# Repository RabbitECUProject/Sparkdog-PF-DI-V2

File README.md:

# Sparkdog-PF-DI-V2
KiCad project for hardware development of Sparkdog PF-DI PCB. The Sparkdog PF-DI PCB can be used as a plug in PCB for the Rabbit ECU, extending the functionality to include:

1. Either Teensy 3.5 MK64 or MK10 processor, or both
2. 4 x Direct injection driver circuit
3. 2 x knock input circuit
4. 1 x 4-channel H-Bridge driver
5. 4 VVT input channels in addition to the Rabbit ECU Crank/Cam inputs
6. PIC18F26 stay-alive processor for can wake-up function

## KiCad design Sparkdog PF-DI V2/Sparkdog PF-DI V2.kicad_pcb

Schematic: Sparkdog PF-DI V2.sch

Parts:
C100: 0603 100nF; RESC1608X55N
J1, J3, J5: Conn_01x06_Female; SIP-6
J2, J4: Conn_01x08_Female; SIP-8
R100, R101: 0603 1k; RESC1608X55N
RN100, RN104, RN106: 1206 10k; 742C083103JP
RN101, RN102, RN103, RN105: 1206 1k; 742C083103JP
U2: Arduino_Footprint; ARDUINO_DUE

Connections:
/3 TEENSY/GDI1_SIG: RN100.3 (R3.1); also elsewhere on the board
/3 TEENSY/GDI2_SIG: RN100.4 (R4.1); also elsewhere on the board
/3 TEENSY/UART_RX_SIG: RN100.2 (R2.1); also elsewhere on the board
/3 TEENSY/UART_TX_SIG: RN100.1 (R1.1); also elsewhere on the board
/6 ETC PROCESSOR/A12: RN105.1 (R1.1), RN105.2 (R2.1); also elsewhere on the board
/7 POWER/SIG_CANH: J4.8; also elsewhere on the board
/7 POWER/SIG_CANL: J4.7; also elsewhere on the board
/7 POWER/SIG_KAL: J4.6; also elsewhere on the board
/ACH: U2.11; also elsewhere on the board
/ACL: U2.12; also elsewhere on the board
/ATS: U2.14; also elsewhere on the board
/BATT: U2.19; also elsewhere on the board
/CAN_RX: U2.23; also elsewhere on the board
/CAN_TX: U2.24; also elsewhere on the board
/CKPS_SIG: RN103.7 (R2.2), U2.71; also elsewhere on the board
/CMPS_SIG: RN103.8 (R1.2), U2.72; also elsewhere on the board
/CTS: U2.13; also elsewhere on the board
/DAC_UEGO: RN106.8 (R1.2), U2.22; also elsewhere on the board
/DCH: U2.9; also elsewhere on the board
/DCL: U2.10; also elsewhere on the board
/ETC_1A: R101.2, RN101.8 (R1.2); also elsewhere on the board
/ETC_1B: RN101.7 (R2.2); also elsewhere on the board
/ETC_2A: RN101.6 (R3.2); also elsewhere on the board
/ETC_2B: RN101.5 (R4.2); also elsewhere on the board
/ETC_O1A: J2.5; also elsewhere on the board
/ETC_O1B: J2.6; also elsewhere on the board
/ETC_O2A: J2.7; also elsewhere on the board
/ETC_O2B: J2.8; also elsewhere on the board
/GDI1_SIG_s: RN100.6 (R3.2), RN103.1 (R1.1); also elsewhere on the board
/GDI2_SIG_s: RN100.5 (R4.2), RN103.2 (R2.1); also elsewhere on the board
/HMEN: R101.1, U2.53; also elsewhere on the board
/HMF: U2.61
/HS1EN: U2.40; also elsewhere on the board
/HS2EN: U2.37; also elsewhere on the board
/HYSTHAB: U2.45; also elsewhere on the board
/HYSTLAB: U2.46; also elsewhere on the board
/IEN: U2.42; also elsewhere on the board
/IGT1_SIG: RN101.1 (R1.1), U2.76; also elsewhere on the board
/IGT2_SIG: RN101.2 (R2.1), U2.75; also elsewhere on the board
/IGT3_SIG: RN101.3 (R3.1), U2.74; also elsewhere on the board
/IGT4_SIG: RN101.4 (R4.1), U2.73; also elsewhere on the board
/INJ1_SIG: RN102.1 (R1.1), U2.82; also elsewhere on the board
/INJ2_SIG: RN102.2 (R2.1), U2.81; also elsewhere on the board
/INJ3_SIG: RN102.3 (R3.1), U2.80; also elsewhere on the board
/INJ4_SIG: RN102.4 (R4.1), U2.79; also elsewhere on the board
/M1EN: U2.58; also elsewhere on the board
/M2EN: U2.56; also elsewhere on the board
/MISO: U2.87; also elsewhere on the board
/MOSI: U2.91; also elsewhere on the board
/PPSM: U2.20; also elsewhere on the board
/PPSS: U2.16; also elsewhere on the board
/PUAEN: U2.51; also elsewhere on the board
/PUBEN: U2.36; also elsewhere on the board
/PUMP_PWM: J1.6; also elsewhere on the board
/PWIOA+: J1.5; also elsewhere on the board
/PWIOAB-: J1.3; also elsewhere on the board
/PWIOB+: J3.6; also elsewhere on the board
/PWIOC+: J5.5; also elsewhere on the board
/PWIOCD-: J1.4; also elsewhere on the board
/PWIOD+: J5.6; also elsewhere on the board
/REL_CS: U2.57; also elsewhere on the board
/REL_RST: R100.1, U2.55
/RPS: U2.18; also elsewhere on the board
/SCLK: U2.88; also elsewhere on the board
/SIGAB_HVEN: RN104.8 (R1.2); also elsewhere on the board
/SIGAB_PEAK: RN102.8 (R1.2); also elsewhere on the board
/SIGAB_PWM: RN102.7 (R2.2); also elsewhere on the board
/SIGCD_HVEN: RN104.7 (R2.2); also elsewhere on the board
/SIGCD_PEAK: RN102.6 (R3.2); also elsewhere on the board
/SIGCD_PWM: RN102.5 (R4.2); also elsewhere on the board
/SIG_K1IN: J2.3; also elsewhere on the board
/SIG_K2IN: J2.4; also elsewhere on the board
/SIG_VVTB_OUT: RN106.5 (R4.2); also elsewhere on the board
/SWH: RN104.1 (R1.1), U2.44; also elsewhere on the board
/SWL: RN104.2 (R2.1), U2.43; also elsewhere on the board
/TPSM: U2.17; also elsewhere on the board
/TPSS: U2.15; also elsewhere on the board
/UART_RX: RN100.7 (R2.2); also elsewhere on the board
/UART_TX: RN100.8 (R1.2); also elsewhere on the board
/VRAEN: U2.34; also elsewhere on the board
/VRBEN: U2.33; also elsewhere on the board
/VSDC: U2.27; also elsewhere on the board
/VVT_INP1: J3.3; also elsewhere on the board
/VVT_INP2: J3.4; also elsewhere on the board
/VVT_INP3: J5.3; also elsewhere on the board
/VVT_INP4: J5.4; also elsewhere on the board
unnamed: C100.2, RN106.1 (R1.1), RN106.2 (R2.1)
unnamed: RN106.3 (R3.1), RN106.4 (R4.1)
unnamed: RN106.6 (R3.2), RN106.7 (R2.2)
VBATT: J2.1; also elsewhere on the board
VCC3V3: R100.2, U2.4; also elsewhere on the board
VCC5V: RN105.8 (R1.2), U2.5, U2.59, U2.60, U2.92; also elsewhere on the board
VCC12VP: U2.8; also elsewhere on the board
VCC12VPP: J1.2; also elsewhere on the board
VSS: C100.1, J1.1, J2.2, RN105.7 (R2.2), U2.6, U2.7, U2.25, U2.26, U2.90; also elsewhere on the board

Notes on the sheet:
ALTERNATE SIGNAL BUS WHEN TEENSY NOT USED
OVERRIDE NO T3.5
ARDUINO FOOTPRINT ON RABBIT ECU PCB - USED AS GENERIC PLUG IN INTERFACE
3.3v RAIL OUTPUT TO RABBIT ECU
5.0V RAIL INPUT FROM RABBIT ECU
SHEET 1 MASTER SHEET 2 VVT SHEET 3 TEENSY SHEET 4 KNOCK SHEET 5 ETC SHEET 6 ETC PROCESSOR SHEET 7 POWER SHEET 8 GDI SHEET 9 GDI CONTROL
RC PWM to VOLT converter when T3.5 not used

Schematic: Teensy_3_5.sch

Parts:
D300, D301: 0805 LED; RESC2012X60N
RN300: 1206 1k; 742C083103JP
U300: Teensy_3_5; TEENSY_3_5

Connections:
/2 VVT/PULLEN_AB: U300.26; also elsewhere on the board
/3 TEENSY/GDI1_SIG: U300.30; also elsewhere on the board
/3 TEENSY/GDI2_SIG: U300.29; also elsewhere on the board
/3 TEENSY/REL_RST: U300.62
/3 TEENSY/UART_RX_SIG: U300.3; also elsewhere on the board
/3 TEENSY/UART_TX_SIG: U300.2; also elsewhere on the board
/ACH: U300.67; also elsewhere on the board
/ACL: U300.68; also elsewhere on the board
/BATT: U300.41; also elsewhere on the board
/CAN_RX: U300.6; also elsewhere on the board
/CAN_TX: U300.5; also elsewhere on the board
/CKPS_SIG: U300.28; also elsewhere on the board
/CMPS_SIG: U300.27; also elsewhere on the board
/CTS: U300.37; also elsewhere on the board
/DAC_UEGO: U300.32; also elsewhere on the board
/GDI_SEL: U300.20; also elsewhere on the board
/HMEN: U300.63; also elsewhere on the board
/HS1EN: U300.24; also elsewhere on the board
/HS2EN: U300.23; also elsewhere on the board
/HYSTHAB: U300.66; also elsewhere on the board
/HYSTLAB: U300.65; also elsewhere on the board
/IEN: U300.51; also elsewhere on the board
/IGT1_SIG: U300.11; also elsewhere on the board
/IGT2_SIG: U300.12; also elsewhere on the board
/IGT3_SIG: U300.21; also elsewhere on the board
/IGT4_SIG: U300.22; also elsewhere on the board
/INJ1_SIG: U300.7; also elsewhere on the board
/INJ2_SIG: U300.8; also elsewhere on the board
/INJ3_SIG: U300.9; also elsewhere on the board
/INJ4_SIG: U300.10; also elsewhere on the board
/M1EN: U300.59; also elsewhere on the board
/M2EN: U300.61; also elsewhere on the board
/MISO: U300.54; also elsewhere on the board
/MOSI: U300.53; also elsewhere on the board
/PPSM: U300.31; also elsewhere on the board
/PPSS: U300.38; also elsewhere on the board
/PUAEN: U300.64; also elsewhere on the board
/PUBEN: U300.56; also elsewhere on the board
/REL_CS: U300.60; also elsewhere on the board
/RPS: U300.40; also elsewhere on the board
/SCLK: U300.55; also elsewhere on the board
/SIG_GDIP_EN: U300.4; also elsewhere on the board
/SIG_PUMP_EN: U300.35; also elsewhere on the board
/SIG_VVT1_IN: U300.45; also elsewhere on the board
/SIG_VVT2_IN: U300.44; also elsewhere on the board
/SIG_VVT3_IN: U300.43; also elsewhere on the board
/SIG_VVT4_IN: U300.42; also elsewhere on the board
/SIG_VVTA_OUT: U300.36; also elsewhere on the board
/SWH: RN300.8 (R1.2), U300.49; also elsewhere on the board
/SWL: RN300.7 (R2.2), U300.50; also elsewhere on the board
/TPSM: U300.39; also elsewhere on the board
/TPSS: U300.25; also elsewhere on the board
/VRAEN: U300.57; also elsewhere on the board
/VRBEN: U300.58; also elsewhere on the board
/VSDC: U300.33; also elsewhere on the board
unnamed: D300.2 (A), RN300.4 (R4.1)
unnamed: D301.2 (A), RN300.3 (R3.1)
unnamed: RN300.5 (R4.2), U300.19
unnamed: RN300.6 (R3.2), U300.18
VCC3V3: U300.15, U300.46; also elsewhere on the board
VCC5V: RN300.1 (R1.1), U300.48; also elsewhere on the board
VSS: D300.1 (K), D301.1 (K), RN300.2 (R2.1), U300.1, U300.34, U300.47; also elsewhere on the board

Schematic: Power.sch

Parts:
C700: 0603 100nF; RESC1608X55N
C701, C702: 0603 10pF; RESC1608X55N
CD700, CD701, CD703, CD705, CD706, CD708, CD710, CD712, CD713, CD714: 0603 100nF; RESC1608X55N
CD702, CD704, CD707, CD711: CAP4mm 4.7uF; CAPAE430X550N
CD709: CAP17mm; CAPAE1700X1700N
D700: BYG22B; DIOM5127X229N
J700: SSM-106-L-SV; SSM106LSV; Mouser Part Number 200-SSM106LSV
L700, L701: 0805 10nH; RESC2012X60N
L702: SRN8040-680; INDC8566X410N
R700, R701, R706: 0603 1k; RESC1608X55N
R702, R703: 0603 22k; RESC1608X55N
R704: 2512 1R; RESC6331X75N
R705: 0603 100k; RESC1608X55N
U700, U703: BD433M5FP-CE2; MDAC-TO-252-3; Mouser Part Number 755-BD433M5FP-CE2
U701: PIC18F26J50T-I_ML; PIC18F26; Mouser Part Number 579-PIC18F26J50T-IML
U702: TCAN334; SOIC127P600X175-8N
U704: LM2577SX-ADJ_NOPB; KTT0005B; Mouser Part Number 926-LM2577SXADJNOPB
X700: 4 MHz; ECS49205PXTR

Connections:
/7 POWER/SIG_CANH: U702.7 (CANH); also elsewhere on the board
/7 POWER/SIG_CANL: U702.6 (CANL); also elsewhere on the board
/7 POWER/SIG_KAL: U701.1; also elsewhere on the board
/GDI_SEL: R705.2; also elsewhere on the board
/SIG_K1O: U701.10; also elsewhere on the board
/SIG_K2O: U701.28; also elsewhere on the board
/SIG_KTX: U701.14; also elsewhere on the board
unnamed: C700.1, R700.2
unnamed: C701.1, U701.6, X700.1
unnamed: C702.1, U701.7, X700.2
unnamed: CD709.1, D700.1 (K), R703.1, R704.2
unnamed: CD714.1, U701.3
unnamed: D700.2 (A), L702.2, U704.4 (SWITCH)
unnamed: J700.1, R706.2, U701.26
unnamed: J700.4, U701.25
unnamed: J700.5, U701.24
unnamed: R700.1, U704.1 (COMP)
unnamed: R701.2, R702.2, U704.2 (FEEDBACK)
unnamed: R702.1, R703.2
unnamed: R705.1, U701.2
unnamed: U701.19, U702.8 (STB)
unnamed: U701.20, U702.5 (SHDN)
unnamed: U701.21, U702.4 (RXD)
unnamed: U701.23, U702.1 (TXD)
VBATT: CD712.2, U703.1 (VCC); also elsewhere on the board
VCC3V3: CD701.2, CD703.2, CD704.1, J700.2, L701.2, U700.3 (VOUT); also elsewhere on the board
VCC3V3K: CD706.1, CD707.1, CD708.1, CD713.2, U701.17, U702.3 (VCC), U703.3 (VOUT)
VCC12VP: CD700.1, CD702.1, U700.1 (VCC); also elsewhere on the board
VCC12VPP: CD710.1, CD711.1, L702.1, U704.5 (VIN); also elsewhere on the board
VCC50VPP: R704.1; also elsewhere on the board
VCCA3V3: CD705.2, L701.1; also elsewhere on the board
VSS: C700.2, C701.2, C702.2, CD700.2, CD701.1, CD702.2, CD703.1, CD704.2, CD706.2, CD707.2, CD708.2, CD709.2, CD710.2, CD711.2, CD712.1, CD713.1, CD714.2, J700.3, L700.2, R701.1, U700.2 (N.C.), U701.5, U701.16, U701.29, U702.2 (GND), U703.2 (N.C.), U704.3 (GND_1), U704.6 (GND_2); also elsewhere on the board
VSSA: CD705.1, L700.1; also elsewhere on the board
uC_RESET: R706.1; also elsewhere on the board

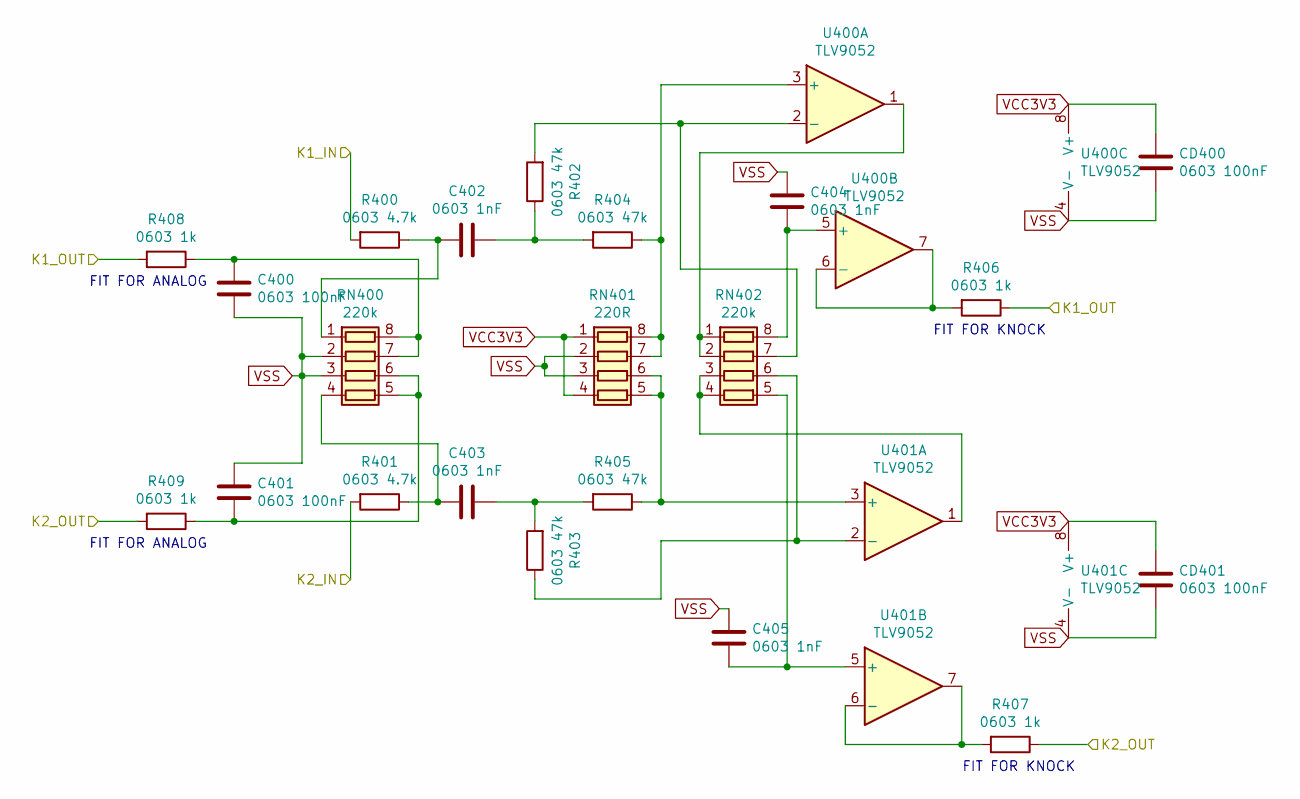
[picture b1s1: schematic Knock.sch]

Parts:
C400, C401: 0603 100nF; RESC1608X55N
C402, C403, C404, C405: 0603 1nF; RESC1608X55N
CD400, CD401: 0603 100nF; RESC1608X55N
R400, R401: 0603 4.7k; RESC1608X55N
R402, R403, R404, R405: 0603 47k; RESC1608X55N
R406, R407, R408, R409: 0603 1k; RESC1608X55N
RN400, RN402: 220k; 742C083103JP
RN401: 220R; 742C083103JP
U400, U401: TLV9052; SOT65P280X110-8N

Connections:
/SIG_K1IN: R400.2; also elsewhere on the board
/SIG_K1O: R406.1, R408.2; also elsewhere on the board
/SIG_K2IN: R401.2; also elsewhere on the board
/SIG_K2O: R407.1, R409.2; also elsewhere on the board
unnamed: C400.1, R408.1, RN400.7 (R2.2), RN400.8 (R1.2)
unnamed: C401.2, R409.1, RN400.5 (R4.2), RN400.6 (R3.2)
unnamed: C402.1, R402.1, R404.2
unnamed: C402.2, R400.1, RN400.1 (R1.1)
unnamed: C403.1, R403.2, R405.2
unnamed: C403.2, R401.1, RN400.4 (R4.1)
unnamed: C404.2, RN402.8 (R1.2), U400.5 (+)
unnamed: C405.2, RN402.5 (R4.2), U401.5 (+)
unnamed: R402.2, RN402.7 (R2.2), U400.2 (-)
unnamed: R403.1, RN402.6 (R3.2), U401.2 (-)
unnamed: R404.1, RN401.7 (R2.2), RN401.8 (R1.2), U400.3 (+)
unnamed: R405.1, RN401.5 (R4.2), RN401.6 (R3.2), U401.3 (+)
unnamed: R406.2, U400.6 (-), U400.7
unnamed: R407.2, U401.6 (-), U401.7
unnamed: RN402.1 (R1.1), RN402.2 (R2.1), U400.1
unnamed: RN402.3 (R3.1), RN402.4 (R4.1), U401.1
VCC3V3: CD400.1, CD401.1, RN401.1 (R1.1), RN401.4 (R4.1), U400.8 (V+), U401.8 (V+); also elsewhere on the board
VSS: C400.2, C401.1, C404.1, C405.1, CD400.2, CD401.2, RN400.2 (R2.1), RN400.3 (R3.1), RN401.2 (R2.1), RN401.3 (R3.1), U400.4 (V-), U401.4 (V-); also elsewhere on the board

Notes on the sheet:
FIT FOR KNOCK
FIT FOR ANALOG

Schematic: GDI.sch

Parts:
D800, D802, D803, D805, D850, D852, D853: DO-214AC SCHOTTKY; DIOM5127X229N
D801, D804, D851: DO-214AC 81V; DIOM5127X229N
R800, R850: 0603 470R; RESC1608X55N
R801, R851: 1206 4.7k; RESC3216X60N
R802, R852: 2512 0.05R; RESC6331X75N
R803, R805, R808, R809, R812, R853, R855, R858, R859: 0603 10k; RESC1608X55N
R804, R806, R854, R856: 0603 4.7k; RESC1608X55N
R807, R857: 0603 1k; RESC1608X55N
R810: 2512 0.2R; RESC6331X75N
R811: 0603 220R; RESC1608X55N
U800, U801, U802, U850, U851, U852: DDC113TU; SOT-363-6
U803, U804, U810, U811, U853, U854: STD7NK40Z; MDAC-TO-252-3
U805, U806, U807, U808, U855, U856, U857, U858: SUD19P06-60; MDAC-TO-252-3
U809: Dual_Trans_Array_NPN; SOT-363-6

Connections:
/8 GDI/SIG_12V_HSSA: R805.2, U800.6, U806.1 (G)
/8 GDI/SIG_12V_HSSB: R808.2, U800.3, U807.1 (G)
/8 GDI/SIG_12V_HSSC: R855.2, U850.6, U856.1 (G)
/8 GDI/SIG_12V_HSSD: R858.2, U850.3, U857.1 (G)
/8 GDI/SIG_HV_HSSA: R803.1, R804.2, U805.1 (G)
/8 GDI/SIG_HV_HSSB: R806.2, R809.1, U808.1 (G)
/8 GDI/SIG_HV_HSSC: R853.1, R854.2, U855.1 (G)
/8 GDI/SIG_HV_HSSD: R856.2, R859.1, U858.1 (G)
/8 GDI/SIG_PUMP_PWMS: R811.2; also elsewhere on the board
/8 GDI/SIG_PWM_LSAB_s: R800.1, U802.3, U803.1 (G)
/8 GDI/SIG_PWM_LSCD_s: R850.1, U852.3, U853.1 (G)
/9 GDI CONTROL/SIGAB_LS_EN: R800.2; also elsewhere on the board
/9 GDI CONTROL/SIGA_HV_EN: U801.2; also elsewhere on the board
/9 GDI CONTROL/SIGB_HV_EN: U801.5; also elsewhere on the board
/9 GDI CONTROL/SIGB_LV_EN: U800.5; also elsewhere on the board
/9 GDI CONTROL/SIGCD_LS_EN: R850.2; also elsewhere on the board
/9 GDI CONTROL/SIGC_HV_EN: U851.2; also elsewhere on the board
/9 GDI CONTROL/SIGD_HV_EN: U851.5; also elsewhere on the board
/9 GDI CONTROL/SIGD_LV_EN: U850.5; also elsewhere on the board
/GDI1_SIG_s: U802.2; also elsewhere on the board
/GDI2_SIG_s: U852.2; also elsewhere on the board
/PUMP_PWM: D804.1 (K), D805.2 (A), R812.2, U810.2 (D); also elsewhere on the board
/PWIOA+: D802.1 (K), U805.2 (D); also elsewhere on the board
/PWIOAB-: D800.2 (A), D801.1 (K), R801.1, U803.2 (D); also elsewhere on the board
/PWIOB+: D803.1 (K), U808.2 (D); also elsewhere on the board
/PWIOC+: D852.1 (K), U855.2 (D); also elsewhere on the board
/PWIOCD-: D850.2 (A), D851.1 (K), R851.1, U853.2 (D); also elsewhere on the board
/PWIOD+: D853.1 (K), U858.2 (D); also elsewhere on the board
/SIGAB_IF: R807.2; also elsewhere on the board
/SIGAB_LVEN: U800.2; also elsewhere on the board
/SIGCD_IF: R857.2; also elsewhere on the board
/SIGCD_LVEN: U850.2; also elsewhere on the board
/SIG_PUMP_EN: U809.2; also elsewhere on the board
/SIG_PUMP_IF: R810.2, U809.5, U810.3 (S); also elsewhere on the board
unnamed: D800.1 (K), U804.2 (D)
unnamed: D802.2 (A), U806.2 (D)
unnamed: D803.2 (A), U807.2 (D)
unnamed: D805.1 (K), U811.2 (D)
unnamed: D850.1 (K), U854.2 (D)
unnamed: D852.2 (A), U856.2 (D)
unnamed: D853.2 (A), U857.2 (D)
unnamed: R801.2, U802.6, U804.1 (G)
unnamed: R802.2, R807.1, U802.5, U803.3 (S)
unnamed: R803.2, U801.6
unnamed: R809.2, U801.3
unnamed: R811.1, U809.3, U810.1 (G)
unnamed: R812.1, U809.6, U811.1 (G)
unnamed: R851.2, U852.6, U854.1 (G)
unnamed: R852.2, R857.1, U852.5, U853.3 (S)
unnamed: R853.2, U851.6
unnamed: R859.2, U851.3
VCC12VPP: R805.1, R808.1, R855.1, R858.1, U804.3 (S), U806.3 (S), U807.3 (S), U811.3 (S), U854.3 (S), U856.3 (S), U857.3 (S); also elsewhere on the board
VCC50VPP: R804.1, R806.1, R854.1, R856.1, U805.3 (S), U808.3 (S), U855.3 (S), U858.3 (S); also elsewhere on the board
VSS: D801.2 (A), D804.2 (A), D851.2 (A), R802.1, R810.1, R852.1, U800.1, U800.4, U801.1, U801.4, U802.1, U802.4, U809.1, U809.4, U850.1, U850.4, U851.1, U851.4, U852.1, U852.4; also elsewhere on the board

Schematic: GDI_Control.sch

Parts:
CD900, CD901, CD902, CD903: 0603 100nF; RESC1608X55N
U900, U901: SN74AHCT02; SOP65P640X110-14N
U902, U903: SN74AHCT08; SOP65P640X110-14N

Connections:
/8 GDI/SIG_PUMP_PWMS: U902.8; also elsewhere on the board
/9 GDI CONTROL/SIGAB_LS_EN: U900.13; also elsewhere on the board
/9 GDI CONTROL/SIGA_HV_EN: U902.6; also elsewhere on the board
/9 GDI CONTROL/SIGB_HV_EN: U902.3; also elsewhere on the board
/9 GDI CONTROL/SIGB_LV_EN: U900.4; also elsewhere on the board
/9 GDI CONTROL/SIGCD_LS_EN: U901.13; also elsewhere on the board
/9 GDI CONTROL/SIGC_HV_EN: U903.6; also elsewhere on the board
/9 GDI CONTROL/SIGD_HV_EN: U903.3; also elsewhere on the board
/9 GDI CONTROL/SIGD_LV_EN: U901.4; also elsewhere on the board
/SIGAB_HVEN: U900.2, U900.3, U902.4; also elsewhere on the board
/SIGAB_LVEN: U900.5, U900.6; also elsewhere on the board
/SIGAB_PEAK: U900.8, U902.2, U902.5; also elsewhere on the board
/SIGAB_PWM: U900.9; also elsewhere on the board
/SIGCD_HVEN: U901.2, U901.3, U903.4; also elsewhere on the board
/SIGCD_LVEN: U901.5, U901.6; also elsewhere on the board
/SIGCD_PEAK: U901.8, U903.2, U903.5; also elsewhere on the board
/SIGCD_PWM: U901.9; also elsewhere on the board
/SIG_GDIP_EN: U902.9, U902.10; also elsewhere on the board
unnamed: U900.1, U902.1
unnamed: U900.10, U900.11, U900.12
unnamed: U901.1, U903.1
unnamed: U901.10, U901.11, U901.12
VCC5V: CD900.1, CD901.1, CD902.1, CD903.1, U900.14, U901.14, U902.12, U902.13, U902.14, U903.9, U903.10, U903.12, U903.13, U903.14; also elsewhere on the board
VSS: CD900.2, CD901.2, CD902.2, CD903.2; also elsewhere on the board

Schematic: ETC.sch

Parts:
C500, C501, C502: 0603 10nF; RESC1608X55N
C503, C504: 0603 100nF; RESC1608X55N
C505, C506: 0805 10uF; RESC2012X60N
CD500: CAP4mm 4.7uF; CAPAE1700X1700N
CD501, CD502: 0603 100nF; RESC1608X55N
D500, D501, D502, D503, D504: 0805 1N4148; RESC2012X60N
R500, R501: 0603 100k; RESC1608X55N
R502, R503: 0603 1k; RESC1608X55N
R504, R505: 2512 0.1R; RESC6331X75N
R506: 0603 100R; RESC1608X55N
R507, R508, R509, R510: 0805 0R; RESC2012X60N
R511: 0603 10k; RESC1608X55N
R512: 0603 47k; RESC1608X55N
R513: 0603 820k; RESC1608X55N
R514: 0603 5M; RESC1608X55N
R515: 0603 470k; RESC1608X55N
RN500: 1206 180k; 742C083103JP
RN501: 1206 10k; 742C083103JP
U500: L6206PD013TR; SOP65P1420X360-37N; Mouser Part Number 511-L6206PD013TR
U501: SUD19P06-60; MDAC-TO-252-3
U502: TL331SN4T3G; SOT95P275X110-5N; Mouser Part Number 863-TL331SN4T3G
U503: Dual_Trans_Array_NPN; SOT-363-6

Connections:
/5 ETC/ETC_ENA: D502.2 (A), R500.2; also elsewhere on the board
/5 ETC/ETC_ENB: D503.2 (A), R501.2; also elsewhere on the board
/5 ETC/ETC_PEN: R511.2, U501.1 (G), U503.6
/5 ETC/VBOOT: C503.2, C504.2, D501.1 (K), U500.30 (VBOOT)
/5 ETC/VCC_ETC: C503.1, C504.1, CD500.1, CD501.2, D500.2 (A), U500.4 (VSA), U500.33 (VSB), U501.2 (D)
/5 ETC/VCP: C502.2, U500.7 (VCP)
/ETC_1A: R509.1, U500.10 (IN1A); also elsewhere on the board
/ETC_1B: R510.1, U500.26 (IN1B); also elsewhere on the board
/ETC_2A: R509.2, U500.11 (IN2A); also elsewhere on the board
/ETC_2B: R510.2, U500.27 (IN2B); also elsewhere on the board
/ETC_IFA: R504.1, U500.12 (SENSEA); also elsewhere on the board
/ETC_IFB: R505.1, U500.25 (SENSEB); also elsewhere on the board
/ETC_O1A: R507.1, U500.15 (OUT1A); also elsewhere on the board
/ETC_O1B: R508.1, U500.22 (OUT1B); also elsewhere on the board
/ETC_O2A: R507.2, U500.5 (OUT2A); also elsewhere on the board
/ETC_O2B: R508.2, U500.32 (OUT2B); also elsewhere on the board
/PPSM: RN500.1 (R1.1); also elsewhere on the board
/TPSM: R512.1, RN500.4 (R4.1); also elsewhere on the board
unnamed: C500.1, R500.1, U500.8 (ENA), U500.13 (OCDA)
unnamed: C501.1, R501.1, U500.24 (OCDB), U500.29 (ENB)
unnamed: C502.1, R506.2
unnamed: C505.2, RN500.7 (R2.2), RN500.8 (R1.2), U502.1 (IN-)
unnamed: C506.1, D504.2 (A), R513.1, R514.2, RN500.5 (R4.2), RN500.6 (R3.2), U502.3 (IN+)
unnamed: D500.1 (K), D501.2 (A), R506.1
unnamed: D502.1 (K), RN501.1 (R1.1)
unnamed: D503.1 (K), RN501.2 (R2.1)
unnamed: D504.1 (K), R512.2
unnamed: R502.1, U500.9 (PROGCLA)
unnamed: R503.2, U500.28 (PROGCLB)
unnamed: R514.1, R515.2, U502.4 (OUT), U503.5
unnamed: RN501.3 (R3.1), RN501.4 (R4.1)
unnamed: RN501.6 (R3.2), RN501.7 (R2.2), RN501.8 (R1.2), U503.2, U503.3
VCC5V: CD502.1, R515.1, U502.5 (VCC); also elsewhere on the board
VCC12VPP: R511.1, U501.3 (S); also elsewhere on the board
VSS: C500.2, C501.2, C505.1, C506.2, CD500.2, CD501.1, CD502.2, R502.2, R503.1, R504.2, R505.2, R513.2, RN500.2 (R2.1), RN500.3 (R3.1), RN501.5 (R4.2), U500.1 (GND_1), U500.18 (GND_2), U500.19 (GND_3), U500.36 (GND_4), U500.37 (EP), U502.2 (VEE), U503.1, U503.4; also elsewhere on the board

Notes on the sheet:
TODO CHANGE TO FET

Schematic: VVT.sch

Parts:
C200, C201, C202, C203: 0603 1nF; RESC1608X55N
CD200: 0603 100nF; RESC1608X55N
D200, D201, D202, D203: BZX84C5V1LT1G; SOT96P237X111-3N; Mouser Part Number 863-BZX84C5V1LT1G
R200, R201: 1206 0.1R; RESC3216X60N
RN200, RN201, RN202, RN204, RN205: 1206 10k; 742C083103JP
RN203: 1206 470R; 742C083103JP
U200: IRF7907TRPBF; SOIC127P600X175-8N; Mouser Part Number 942-IRF7907TRPBF
U201, U202: Dual_Trans_Array_NPN; SOT-363-6
U203, U204: Dual_Trans_Array_PNP; SOT-363-6
U205: 74AHC14PW,118; SOP65P640X110-14N; Mouser Part Number 771-74AHC14PW-T

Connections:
/2 VVT/OUT_VVTA: U200.7 (D2_1), U200.8 (D2_2)
/2 VVT/OUT_VVTB: U200.5 (D1_1), U200.6 (D1_2)
/2 VVT/PULLEN_AB: U201.2, U201.5, U202.2, U202.5; also elsewhere on the board
/2 VVT/VVTA_FB: RN200.1 (R1.1)
/2 VVT/VVTB_FB: RN200.3 (R3.1)
/SIG_VVT1_IN: RN201.2 (R2.1), RN201.3 (R3.1); also elsewhere on the board
/SIG_VVT2_IN: RN202.2 (R2.1), RN202.3 (R3.1); also elsewhere on the board
/SIG_VVT3_IN: RN204.6 (R3.2), RN204.7 (R2.2); also elsewhere on the board
/SIG_VVT4_IN: RN205.6 (R3.2), RN205.7 (R2.2); also elsewhere on the board
/SIG_VVTA_OUT: RN200.2 (R2.1); also elsewhere on the board
/SIG_VVTB_OUT: RN200.4 (R4.1); also elsewhere on the board
/VVT_INP1: RN201.1 (R1.1), RN203.2 (R2.1); also elsewhere on the board
/VVT_INP2: RN202.1 (R1.1), RN203.1 (R1.1); also elsewhere on the board
/VVT_INP3: RN203.4 (R4.1), RN204.8 (R1.2); also elsewhere on the board
/VVT_INP4: RN203.3 (R3.1), RN205.8 (R1.2); also elsewhere on the board
unnamed: C200.2, D200.3 (K), RN201.8 (R1.2), U205.1 (1A)
unnamed: C201.1, D201.3 (K), RN202.8 (R1.2), U205.5 (3A)
unnamed: C202.2, D202.3 (K), RN204.1 (R1.1), U205.13 (6A)
unnamed: C203.1, D203.3 (K), RN205.1 (R1.1), U205.9 (4A)
unnamed: R200.2, RN200.8 (R1.2), U200.1 (S2)
unnamed: R201.1, RN200.6 (R3.2), U200.3 (S1)
unnamed: RN200.5 (R4.2), U200.4 (G1)
unnamed: RN200.7 (R2.2), U200.2 (G2)
unnamed: RN201.5 (R4.2), RN201.6 (R3.2)
unnamed: RN201.7 (R2.2), U205.2 (1Y), U205.3 (2A)
unnamed: RN202.5 (R4.2), RN202.6 (R3.2)
unnamed: RN202.7 (R2.2), U205.6 (3Y)
unnamed: RN203.5 (R4.2), U204.6
unnamed: RN203.6 (R3.2), U204.3
unnamed: RN203.7 (R2.2), U203.6
unnamed: RN203.8 (R1.2), U203.3
unnamed: RN204.2 (R2.1), U205.12 (6Y)
unnamed: RN204.3 (R3.1), RN204.4 (R4.1)
unnamed: RN205.2 (R2.1), U205.8 (4Y)
unnamed: RN205.3 (R3.1), RN205.4 (R4.1)
unnamed: U201.3, U203.2
unnamed: U201.6, U203.5
unnamed: U202.3, U204.2
unnamed: U202.6, U204.5
VCC5V: CD200.1, U203.1, U203.4, U204.1, U204.4, U205.14 (VCC); also elsewhere on the board
VSS: C200.1, C201.2, C202.1, C203.2, CD200.2, D200.1 (A), D201.1 (A), D202.1 (A), D203.1 (A), R200.1, R201.2, RN201.4 (R4.1), RN202.4 (R4.1), RN204.5 (R4.2), RN205.5 (R4.2), U201.1, U201.4, U202.1, U202.4, U205.7 (GND); also elsewhere on the board

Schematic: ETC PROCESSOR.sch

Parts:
C600, C601: 0603 10pF; RESC1608X55N
CD600, CD601, CD602, CD603, CD604, CD605, CD606: 0603 100nF; RESC1608X55N
J600: M50-3610542R; M503610542; Mouser Part Number 855-M50-3610542R
R600, R601: 0603 1k; RESC1608X55N
RN600, RN602, RN603, RN605, RN606: 1206 10k; 742C083103JP
RN601: 1206 100k; 742C083103JP
RN604: 1206 1k; 742C083103JP
U600: MK10DX128VLK7
U601: TLV809EA29DCKR; SOT65P210X110-3N; Mouser Part Number 595-TLV809EA29DCKR
X600: Crystal; ECS49205PXTR

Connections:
/5 ETC/ETC_ENA: U600.52; also elsewhere on the board
/5 ETC/ETC_ENB: U600.71; also elsewhere on the board
/6 ETC PROCESSOR/A12: RN606.3 (R3.1); also elsewhere on the board
/6 ETC PROCESSOR/EZP_DI: J600.8, U600.27
/6 ETC PROCESSOR/GDI_LR: RN604.5 (R4.2), U600.72
/6 ETC PROCESSOR/RESET: J600.10, R600.2, U600.42
/6 ETC PROCESSOR/SWCLK: J600.4, U600.26
/6 ETC PROCESSOR/SWDIO: J600.2, U600.29
/6 ETC PROCESSOR/SWO: J600.6, U600.28
/ACH: RN601.1 (R1.1); also elsewhere on the board
/ACL: RN601.2 (R2.1); also elsewhere on the board
/ATS: RN605.6 (R3.2); also elsewhere on the board
/BATT: RN600.3 (R3.1); also elsewhere on the board
/CTS: RN605.5 (R4.2); also elsewhere on the board
/DCH: RN601.3 (R3.1); also elsewhere on the board
/DCL: RN601.4 (R4.1); also elsewhere on the board
/ETC_1A: U600.43; also elsewhere on the board
/ETC_1B: U600.44; also elsewhere on the board
/ETC_2A: U600.77; also elsewhere on the board
/ETC_2B: U600.78; also elsewhere on the board
/ETC_IFA: U600.45; also elsewhere on the board
/ETC_IFB: U600.46; also elsewhere on the board
/GDI1_SIG_s: U600.79; also elsewhere on the board
/GDI2_SIG_s: U600.80; also elsewhere on the board
/GDI_SEL: RN604.4 (R4.1); also elsewhere on the board
/IEN: RN603.6 (R3.2); also elsewhere on the board
/M1EN: RN603.7 (R2.2); also elsewhere on the board
/M2EN: RN603.8 (R1.2); also elsewhere on the board
/MISO: RN604.2 (R2.1); also elsewhere on the board
/MOSI: RN604.3 (R3.1); also elsewhere on the board
/PPSM: RN600.4 (R4.1); also elsewhere on the board
/PPSS: RN605.8 (R1.2); also elsewhere on the board
/PUAEN: RN602.5 (R4.2); also elsewhere on the board
/PUBEN: RN602.6 (R3.2); also elsewhere on the board
/REL_CS: RN603.5 (R4.2); also elsewhere on the board
/RPS: RN600.2 (R2.1); also elsewhere on the board
/SCLK: RN604.1 (R1.1); also elsewhere on the board
/SIGAB_HVEN: U600.30; also elsewhere on the board
/SIGAB_IF: U600.47; also elsewhere on the board
/SIGAB_LVEN: U600.33; also elsewhere on the board
/SIGAB_PEAK: U600.56; also elsewhere on the board
/SIGAB_PWM: U600.57; also elsewhere on the board
/SIGCD_HVEN: U600.32; also elsewhere on the board
/SIGCD_IF: U600.48; also elsewhere on the board
/SIGCD_LVEN: U600.34; also elsewhere on the board
/SIGCD_PEAK: U600.58; also elsewhere on the board
/SIGCD_PWM: U600.53; also elsewhere on the board
/SIG_K1O: RN606.1 (R1.1); also elsewhere on the board
/SIG_K2O: RN606.2 (R2.1); also elsewhere on the board
/SIG_KTX: R601.2; also elsewhere on the board
/SIG_PUMP_IF: U600.55; also elsewhere on the board
/SIG_VVTB_OUT: U600.54; also elsewhere on the board
/TPSM: RN600.1 (R1.1); also elsewhere on the board
/TPSS: RN605.7 (R2.2); also elsewhere on the board
/UART_RX: U600.5; also elsewhere on the board
/UART_TX: U600.6; also elsewhere on the board
/VRAEN: RN602.7 (R2.2); also elsewhere on the board
/VRBEN: RN602.8 (R1.2); also elsewhere on the board
/VSDC: RN606.4 (R4.1); also elsewhere on the board
unnamed: C600.2, U600.41, X600.1
unnamed: C601.2, U600.40, X600.2
unnamed: R601.1, U600.51
unnamed: RN600.5 (R4.2), U600.4
unnamed: RN600.6 (R3.2), U600.3
unnamed: RN600.7 (R2.2), U600.2
unnamed: RN600.8 (R1.2), U600.1
unnamed: RN601.5 (R4.2), U600.16
unnamed: RN601.6 (R3.2), U600.15
unnamed: RN601.7 (R2.2), U600.14
unnamed: RN601.8 (R1.2), U600.13
unnamed: RN602.1 (R1.1), U600.76
unnamed: RN602.2 (R2.1), U600.75
unnamed: RN602.3 (R3.1), U600.74
unnamed: RN602.4 (R4.1), U600.73
unnamed: RN603.1 (R1.1), U600.64
unnamed: RN603.2 (R2.1), U600.63
unnamed: RN603.3 (R3.1), U600.62
unnamed: RN603.4 (R4.1), U600.61
unnamed: RN604.6 (R3.2), U600.37
unnamed: RN604.7 (R2.2), U600.36
unnamed: RN604.8 (R1.2), U600.35
unnamed: RN605.1 (R1.1), U600.68
unnamed: RN605.2 (R2.1), U600.67
unnamed: RN605.3 (R3.1), U600.66
unnamed: RN605.4 (R4.1), U600.65
unnamed: RN606.5 (R4.2), U600.12
unnamed: RN606.6 (R3.2), U600.11
unnamed: RN606.7 (R2.2), U600.10
unnamed: RN606.8 (R1.2), U600.9
VCC3V3: CD600.1, CD601.2, CD602.1, CD604.1, CD605.2, CD606.1, J600.1, U600.7, U600.38, U600.50, U600.60, U600.70, U601.3 (VDD); also elsewhere on the board
VCCA3V3: CD603.2, U600.17, U600.18; also elsewhere on the board
VSS: C600.1, C601.1, CD600.2, CD601.1, CD602.2, CD604.2, CD605.1, CD606.2, J600.3, J600.5, J600.9, U600.8, U600.39, U600.49, U600.59, U600.69, U601.1 (GND); also elsewhere on the board
VSSA: CD603.1, U600.19, U600.20; also elsewhere on the board
uC_RESET: R600.1, U601.2 (~RESET); also elsewhere on the board

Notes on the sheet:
DEBUG SWD PORT

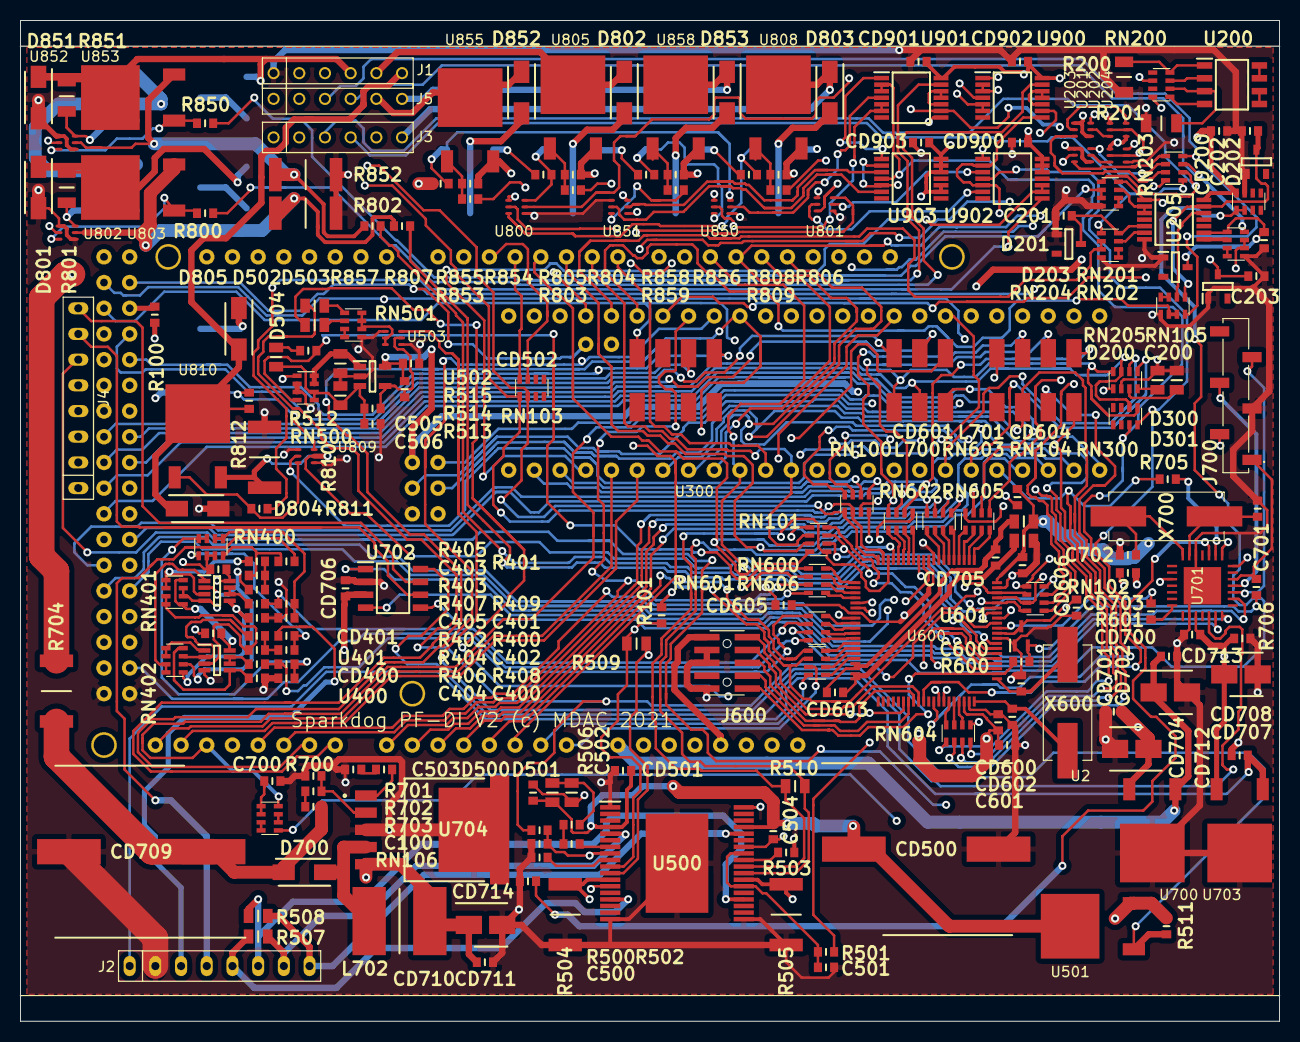
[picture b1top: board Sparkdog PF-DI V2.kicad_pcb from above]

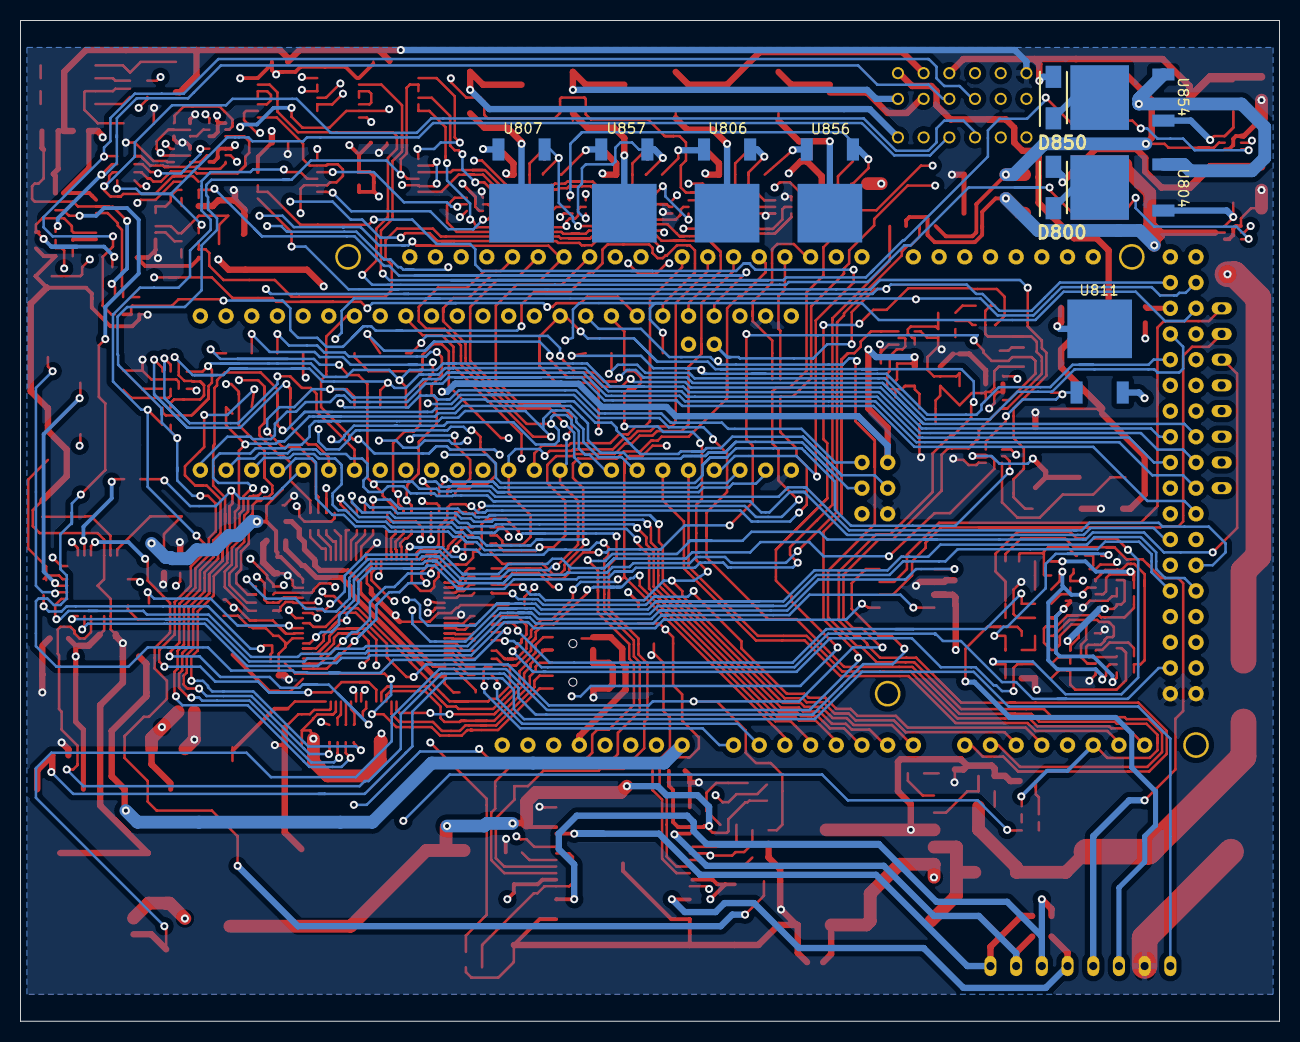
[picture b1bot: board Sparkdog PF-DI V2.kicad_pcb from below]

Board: 4 copper layers, 124.5 x 98.9 mm, 223 parts (9 on the bottom side), 277 nets.

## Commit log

2021-05-16 Commit initial file addition
2021-06-23 Commit schematic changes, new parts library footprints and step files, PCB design file.
2021-07-02 Commit running changes for safekeeping
2021-07-05 Commit updates and Teensy schematic footprint correction.
2021-07-09 Commit for safekeeping
2021-07-21 Commit all files up to 21072021 Gerber and drill outputs.
2023-03-17 Added datasheets
2023-03-17 Added layer prints file
